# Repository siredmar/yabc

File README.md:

yabc
====

This is a repository for a big binary clock

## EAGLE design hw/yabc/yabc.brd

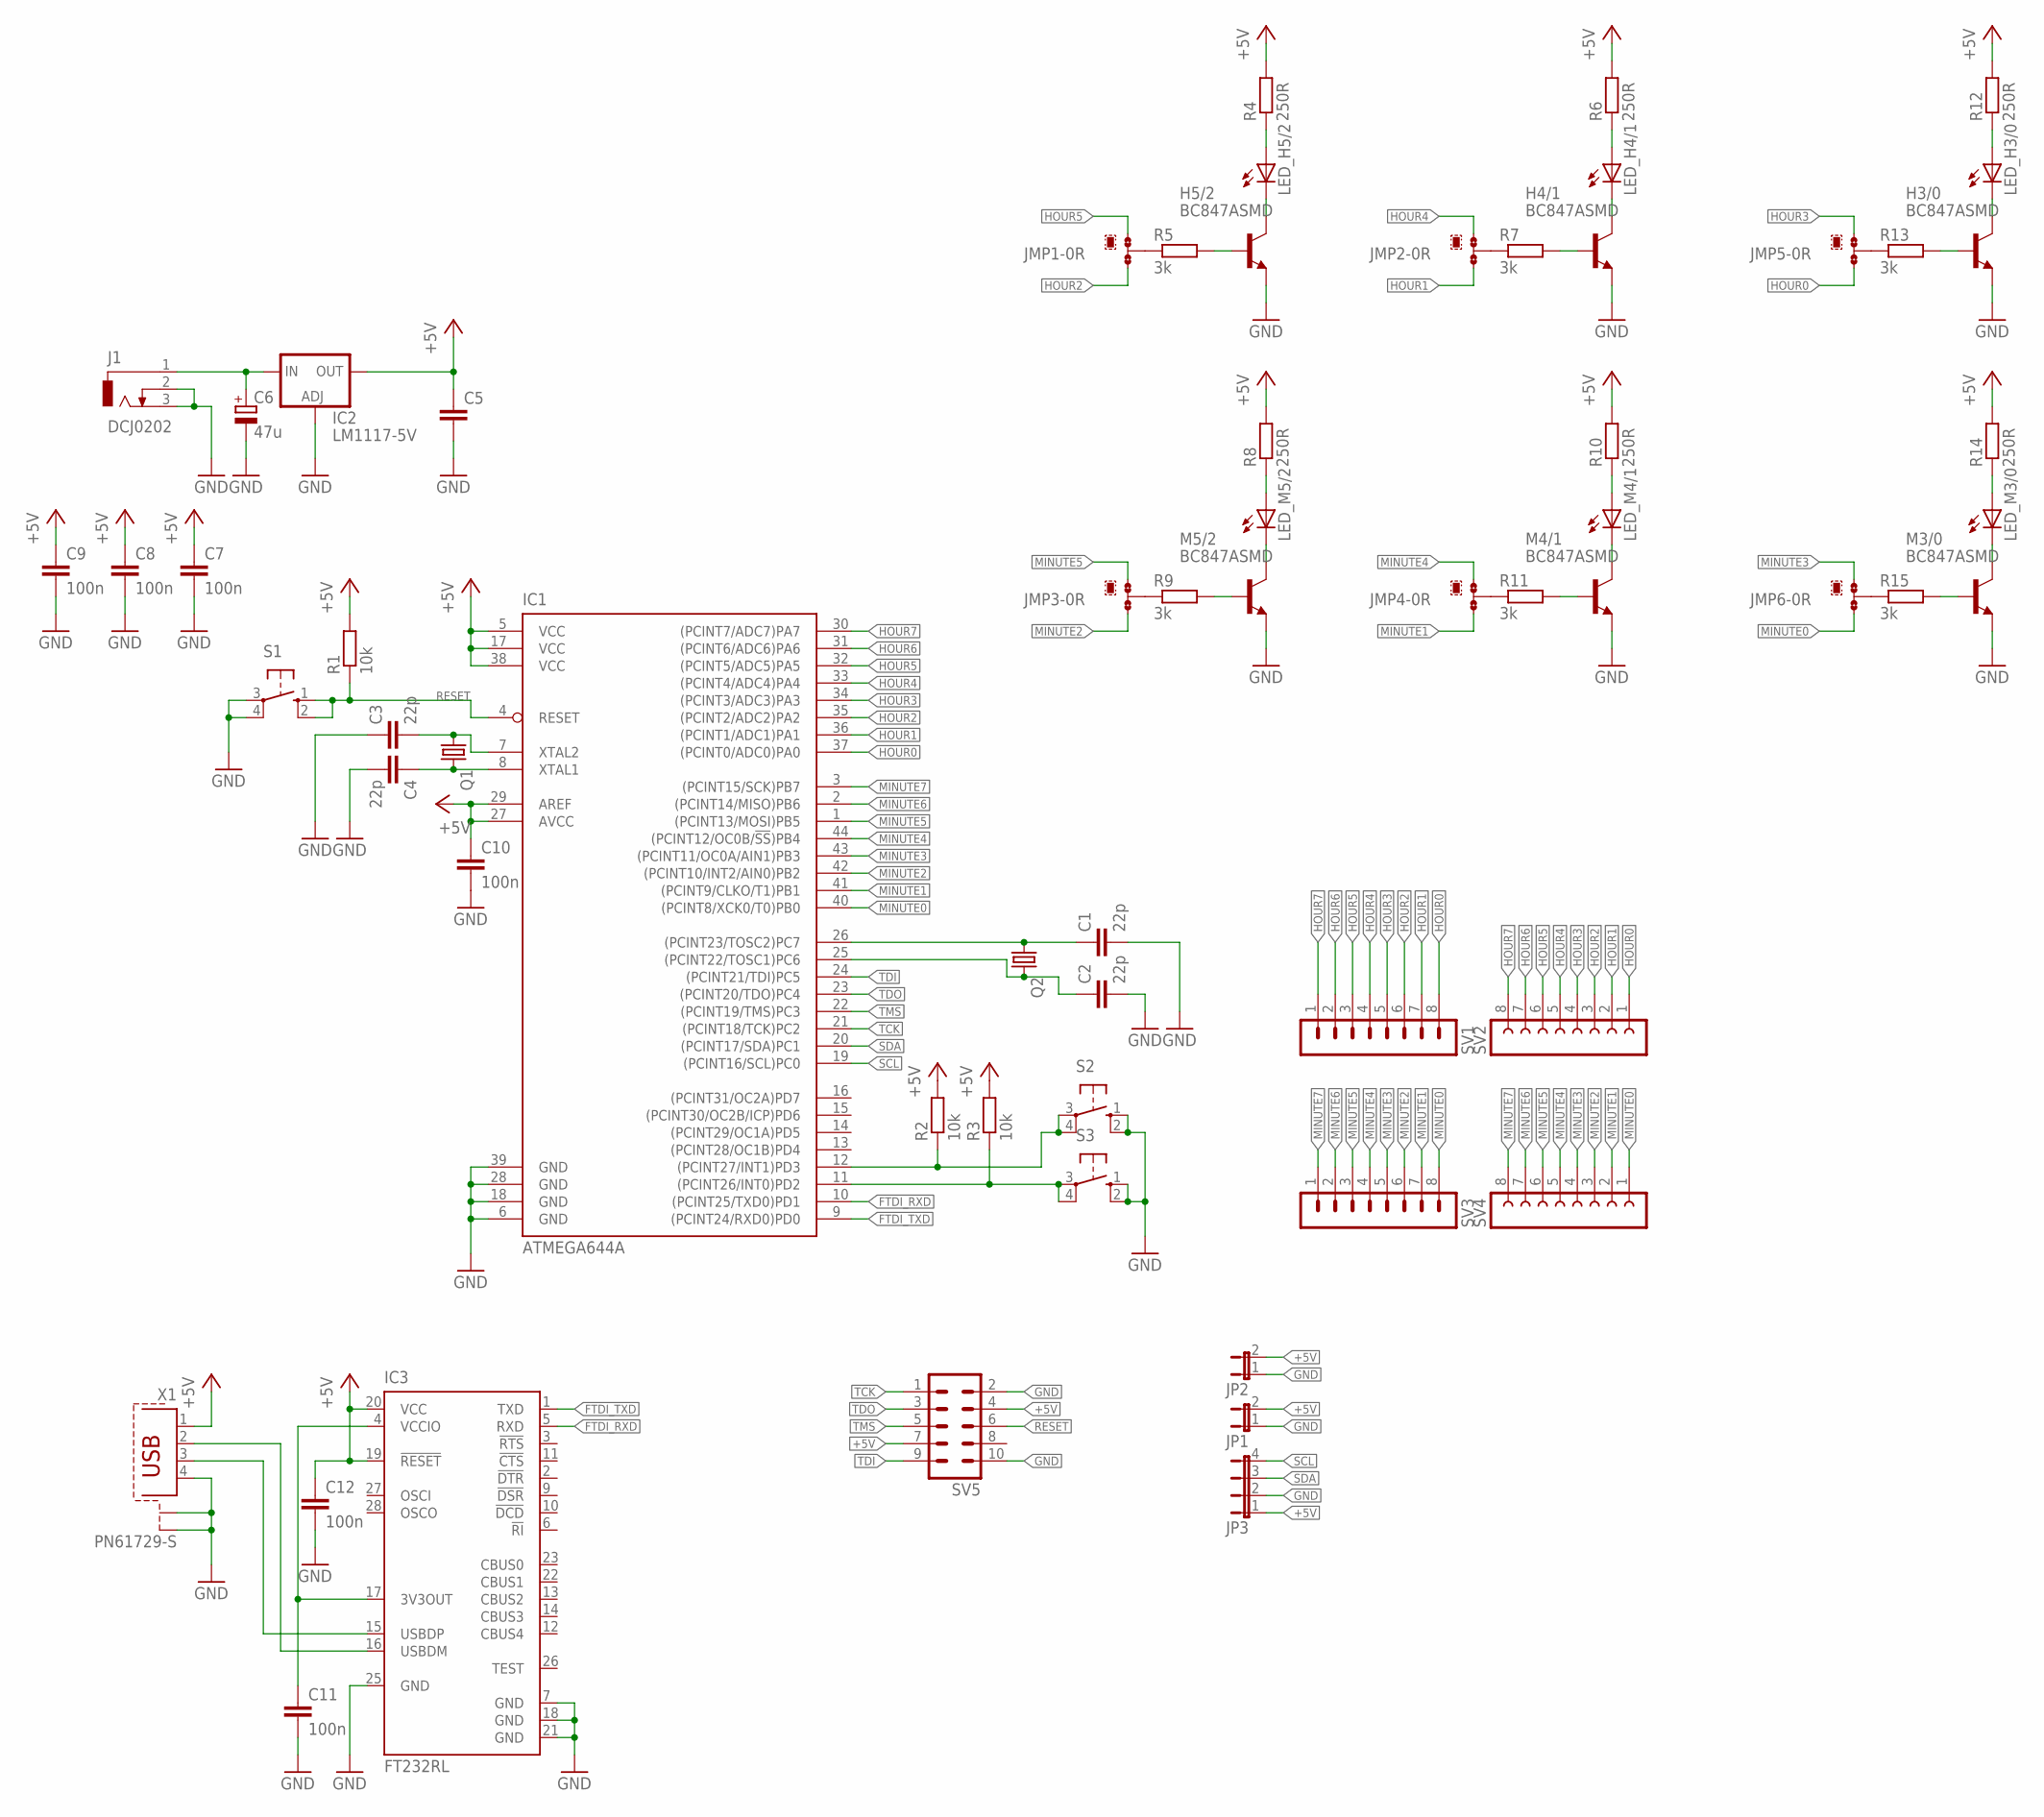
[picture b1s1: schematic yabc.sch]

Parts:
C1, C2, C3, C4: 22p; C0603
C5: C-EUC0805; C0805
C6: 47u; SANYO-OSCON_SMD_B6
C7, C8, C9, C10, C11, C12: 100n; C0603
H3/0, H4/1, H5/2: BC847ASMD; SOT23
IC1: ATMEGA644A; TQFP44
IC2: LM1117-5V; SOT223
IC3: FT232RL; SSOP28
J1: DCJ0202
JMP1, JMP2, JMP3, JMP4, JMP5, JMP6: 0R-JUMPC; C0R-JMP
JP1, JP2: JP1E; JP1
JP3: JP4E; JP4
LED_H3/0, LED_H4/1, LED_H5/2: LED10MM
LED_M3/0, LED_M4/1, LED_M5/2: LED10MM
M3/0, M4/1, M5/2: BC847ASMD; SOT23
Q1: CRYSTALHC49UP; HC49UP
Q2: CRYSTALTC26H; TC26H
R1, R2, R3: 10k; R0603
R4, R6, R8, R10, R12, R14: 250R; R0805
R5, R7, R9, R11, R13, R15: 3k; R0603
S1, S2, S3: 10-XX; B3F-10XX
SV1, SV3: MA08-1W
SV2, SV4: FE08W
SV5: ML10
X1: PN61729-S

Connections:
+5V: C5.1, C7.1, C8.1, C9.1, C10.1, C12.1, IC1.5 (VCC), IC1.17 (VCC), IC1.27 (AVCC), IC1.29 (AREF), IC1.38 (VCC), IC2.4 (OUT), IC3.19 (!RESET), IC3.20 (VCC), JP1.2, JP2.2, JP3.1, R1.2, R2.2, R3.2, R4.2, R6.2, R8.2, R10.2, R12.2, R14.2, SV5.4, SV5.7, X1.1
FTDI_RXD: IC1.10 ((PCINT25/TXD0)PD1), IC3.5 (RXD)
FTDI_TXD: IC1.9 ((PCINT24/RXD0)PD0), IC3.1 (TXD)
GND: C1.2, C2.2, C3.1, C4.2, C5.2, C6.-, C7.2, C8.2, C9.2, C10.2, C11.2, C12.2, H3/0.2 (E), H4/1.2 (E), H5/2.2 (E), IC1.6 (GND), IC1.18 (GND), IC1.28 (GND), IC1.39 (GND), IC2.1 (ADJ), IC3.7 (GND), IC3.18 (GND), IC3.21 (GND), IC3.25 (GND), J1.2, J1.3, JP1.1, JP2.1, JP3.2, M3/0.2 (E), M4/1.2 (E), M5/2.2 (E), S1.3, S1.4 (P1), S2.1 (S), S2.2 (S1), S3.1 (S), S3.2 (S1), SV5.2, SV5.10, X1.4, X1.S1, X1.S2
HOUR0: IC1.37 ((PCINT0/ADC0)PA0), JMP5.3, SV1.8, SV2.1
HOUR1: IC1.36 ((PCINT1/ADC1)PA1), JMP2.3, SV1.7, SV2.2
HOUR2: IC1.35 ((PCINT2/ADC2)PA2), JMP1.3, SV1.6, SV2.3
HOUR3: IC1.34 ((PCINT3/ADC3)PA3), JMP5.1, SV1.5, SV2.4
HOUR4: IC1.33 ((PCINT4/ADC4)PA4), JMP2.1, SV1.4, SV2.5
HOUR5: IC1.32 ((PCINT5/ADC5)PA5), JMP1.1, SV1.3, SV2.6
HOUR6: IC1.31 ((PCINT6/ADC6)PA6), SV1.2, SV2.7
HOUR7: IC1.30 ((PCINT7/ADC7)PA7), SV1.1, SV2.8
MINUTE0: IC1.40 ((PCINT8/XCK0/T0)PB0), JMP6.3, SV3.8, SV4.1
MINUTE1: IC1.41 ((PCINT9/CLKO/T1)PB1), JMP4.3, SV3.7, SV4.2
MINUTE2: IC1.42 ((PCINT10/INT2/AIN0)PB2), JMP3.3, SV3.6, SV4.3
MINUTE3: IC1.43 ((PCINT11/OC0A/AIN1)PB3), JMP6.1, SV3.5, SV4.4
MINUTE4: IC1.44 ((PCINT12/OC0B/!SS!)PB4), JMP4.1, SV3.4, SV4.5
MINUTE5: IC1.1 ((PCINT13/MOSI)PB5), JMP3.1, SV3.3, SV4.6
MINUTE6: IC1.2 ((PCINT14/MISO)PB6), SV3.2, SV4.7
MINUTE7: IC1.3 ((PCINT15/SCK)PB7), SV3.1, SV4.8
unnamed: H5/2.1 (B), R5.2
unnamed: C4.1, IC1.8 (XTAL1), Q1.2
unnamed: C1.1, IC1.26 ((PCINT23/TOSC2)PC7), Q2.1
unnamed: C2.1, IC1.25 ((PCINT22/TOSC1)PC6), Q2.2
unnamed: C6.+, IC2.3 (IN), J1.1
unnamed: LED_H5/2.A, R4.1
unnamed: IC1.11 ((PCINT26/INT0)PD2), R3.1, S3.3, S3.4 (P1)
unnamed: H5/2.3 (C), LED_H5/2.K (C)
unnamed: C3.2, IC1.7 (XTAL2), Q1.1
unnamed: IC3.15 (USBDP), X1.3
unnamed: IC3.16 (USBDM), X1.2
unnamed: C11.1, IC3.4 (VCCIO), IC3.17 (3V3OUT)
unnamed: JMP1.2, R5.1
unnamed: H4/1.1 (B), R7.2
unnamed: LED_H4/1.A, R6.1
unnamed: H4/1.3 (C), LED_H4/1.K (C)
unnamed: JMP2.2, R7.1
unnamed: M5/2.1 (B), R9.2
unnamed: LED_M5/2.A, R8.1
unnamed: LED_M5/2.K (C), M5/2.3 (C)
unnamed: JMP3.2, R9.1
unnamed: M4/1.1 (B), R11.2
unnamed: LED_M4/1.A, R10.1
unnamed: LED_M4/1.K (C), M4/1.3 (C)
unnamed: JMP4.2, R11.1
unnamed: H3/0.1 (B), R13.2
unnamed: LED_H3/0.A, R12.1
unnamed: H3/0.3 (C), LED_H3/0.K (C)
unnamed: JMP5.2, R13.1
unnamed: M3/0.1 (B), R15.2
unnamed: LED_M3/0.A, R14.1
unnamed: LED_M3/0.K (C), M3/0.3 (C)
unnamed: JMP6.2, R15.1
OC2A: IC1.12 ((PCINT27/INT1)PD3), R2.1, S2.3, S2.4 (P1)
RESET: IC1.4 (RESET), R1.1, S1.1 (S), S1.2 (S1), SV5.6
SCL: IC1.19 ((PCINT16/SCL)PC0), JP3.4
SDA: IC1.20 ((PCINT17/SDA)PC1), JP3.3
TCK: IC1.21 ((PCINT18/TCK)PC2), SV5.1
TDI: IC1.24 ((PCINT21/TDI)PC5), SV5.9
TDO: IC1.23 ((PCINT20/TDO)PC4), SV5.3
TMS: IC1.22 ((PCINT19/TMS)PC3), SV5.5

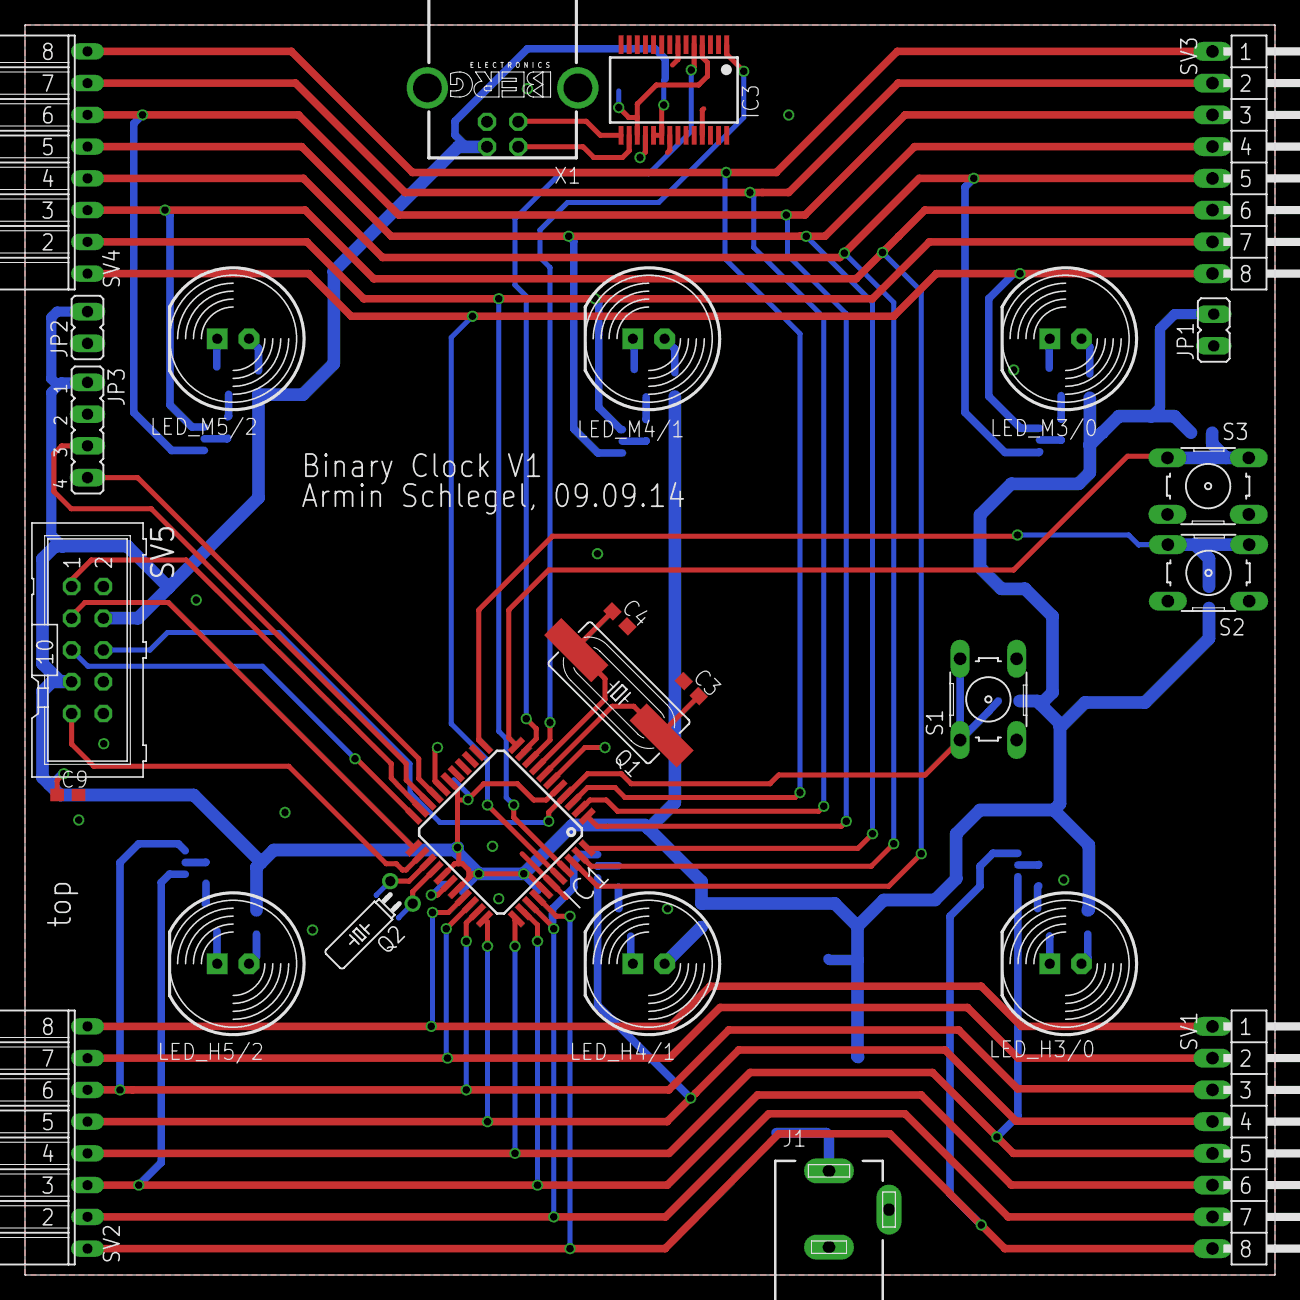
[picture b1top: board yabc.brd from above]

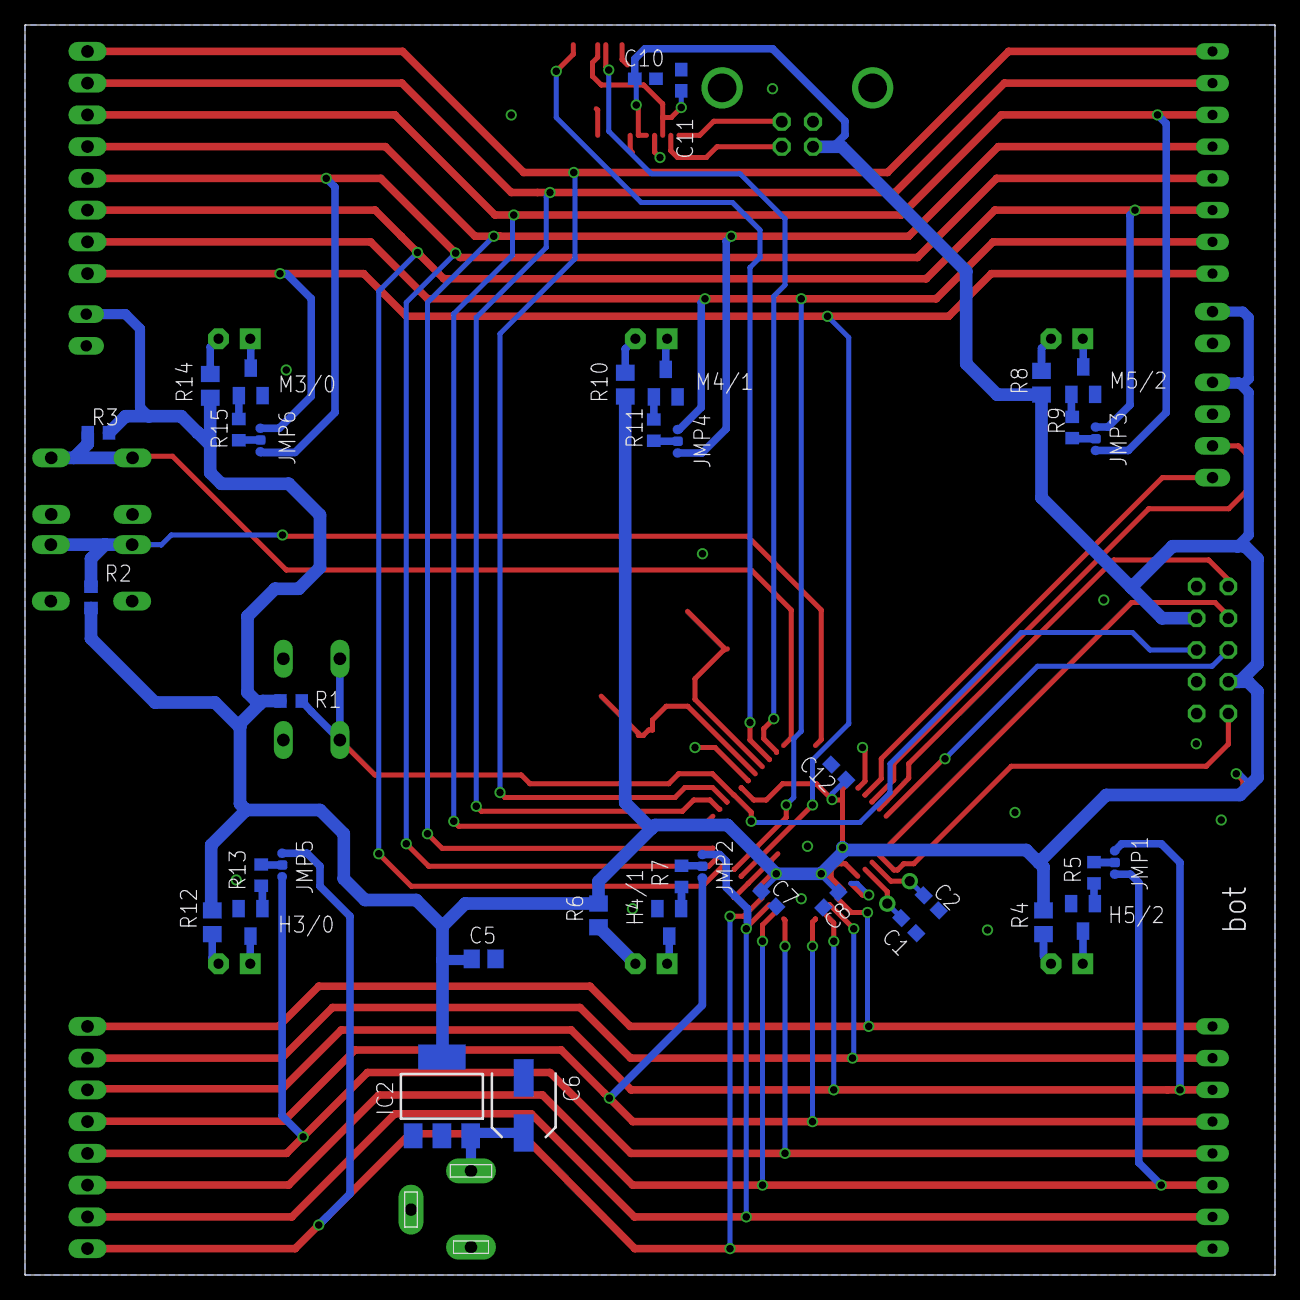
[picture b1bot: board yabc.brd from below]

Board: 2 copper layers, 100.0 x 100.0 mm, 63 parts (37 on the bottom side), 61 nets.

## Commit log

2014-09-09 created directory structure, added v1 of schematic and brd
2014-10-27 clock worky, der jenks wird sich freuen
2014-10-27 code cleanup
2014-10-28 yabc finished
2014-10-28 nicified user interface
2014-10-28 small code cleanup
2014-10-28 added initial value to 1:01 clock
